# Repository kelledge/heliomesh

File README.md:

# Heliomesh

[Documentation](https://kelledge.github.io/heliomesh/)

Heliomesh is a growing collection of PCB designs that enable anyone to build robust solar-power
Meshtastic nodes.

As fun as it is to solder up a solution, these often end up being the weak point of any solution.
This project aims to provide fully integrated solutions that any one can order and pairs nicely
with the existing range of Meshtastic devices and enclosures.

## Contibuting
TODO

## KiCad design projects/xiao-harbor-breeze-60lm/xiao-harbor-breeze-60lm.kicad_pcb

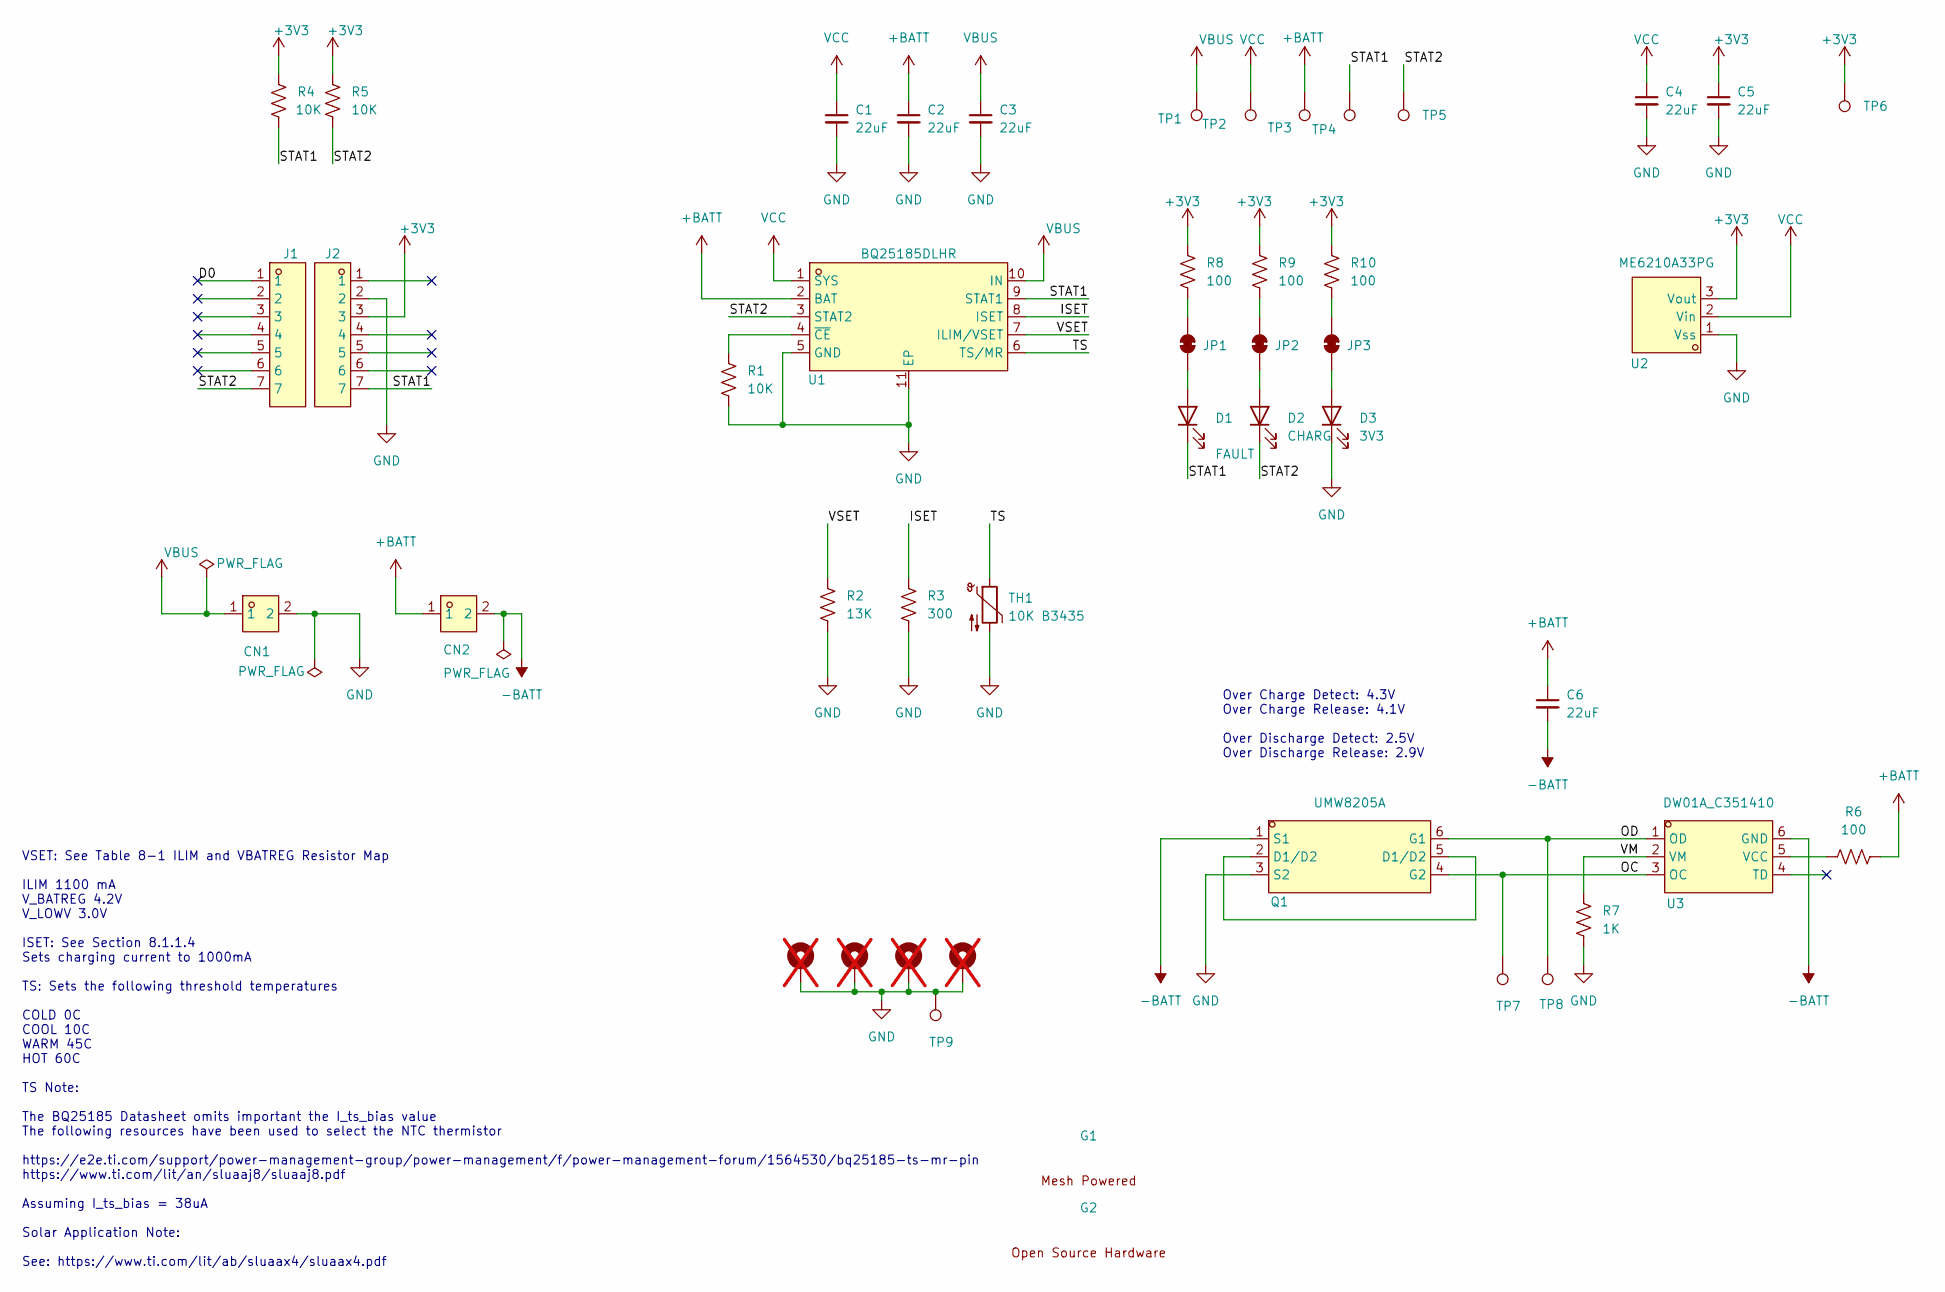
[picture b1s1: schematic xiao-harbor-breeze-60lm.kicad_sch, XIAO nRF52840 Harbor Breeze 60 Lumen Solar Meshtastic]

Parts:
C1, C2, C3, C4, C5, C6: 22uF; C_0805_2012Metric; JLCPCB PN C318688
CN1, CN2: XY122R-5.08-2P; CONN-TH_XY122R-5.08-2P; LCSC Part C784938
D1: FAULT; LED_0603_1608Metric; JLCPCB PN C965799
D2: CHARG; LED_0603_1608Metric; JLCPCB PN C965799
D3: 3V3; LED_0603_1608Metric; JLCPCB PN C965799
G1: mesh_pwrd_very_small
G2: oshw_very_small
H1, H2, H3, H4: MountingHole_Pad; MountingHole_3.2mm_M3_ISO7380_Pad; not fitted
J1, J2: 1165SDIG-07; HDR-TH_7P-P2.54-V-F; LCSC Part C2886701
JP1, JP2, JP3: SolderJumper_2_Bridged; SolderJumper-2_P1.3mm_Bridged_RoundedPad1.0x1.5mm
Q1: UMW8205A; SOT-23-6_L2.9-W1.6-P0.95-LS2.8-BL; LCSC Part C351449
R1, R4, R5: 10K; R_0603_1608Metric; JLCPCB PN C25804
R2: 13K; R_0603_1608Metric; JLCPCB PN C22797
R3: 300; R_0603_1608Metric; JLCPCB PN C23025
R6, R8, R9, R10: 100; R_0603_1608Metric; JLCPCB PN C22775
R7: 1K; R_0603_1608Metric; JLCPCB PN C21190
TH1: 10K B3435; R_0603_1608Metric; JLCPCB PN C153011
TP1, TP2, TP3, TP4, TP5, TP6, TP7, TP8, TP9: TestPoint; TestPoint_Pad_D1.5mm
U1: BQ25185DLHR; WSON-10_L2.2-W2.0-P0.40-BL-EP_TI_DLH0010A; LCSC Part C19725033
U2: ME6210A33PG; SOT-89_L4.5-W2.5-P1.50-LS4.2-BR; LCSC Part C85233
U3: DW01A_C351410; SOT-23-6_L2.9-W1.6-P0.95-LS2.8-BL; LCSC Part C351410

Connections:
+3V3: C5.1, J2.3, R4.1, R5.1, R8.1, R9.1, R10.1, TP6.1, U2.3 (Vout)
+BATT: C2.1, C6.1, CN2.1, R6.2, TP3.1, U1.2 (BAT)
-BATT: C6.2, CN2.2, Q1.1 (S1), U3.6 (GND)
/D0: J1.1
/ISET: R3.1, U1.8 (ISET)
/OC: Q1.4 (G2), TP7.1, U3.3 (OC)
/OD: Q1.6 (G1), TP8.1, U3.1 (OD)
/STAT1: D1.1 (K), J2.7, R4.2, TP4.1, U1.9 (STAT1)
/STAT2: D2.1 (K), J1.7, R5.2, TP5.1, U1.3 (STAT2)
/TS: TH1.1, U1.6 (TS/MR)
/VM: R7.1, U3.2 (VM)
/VSET: R2.1, U1.7 (ILIM/VSET)
GND: C1.2, C2.2, C3.2, C4.2, C5.2, CN1.2, D3.1 (K), H1.1, H2.1, H3.1, H4.1, J2.2, Q1.3 (S2), R1.2, R2.2, R3.2, R7.2, TH1.2, TP9.1, U1.5 (GND), U1.11 (EP), U2.1 (Vss)
unnamed: D1.2 (A), JP1.1 (A)
unnamed: D2.2 (A), JP2.1 (A)
unnamed: D3.2 (A), JP3.1 (A)
unnamed: JP1.2 (B), R8.2
unnamed: JP2.2 (B), R9.2
unnamed: JP3.2 (B), R10.2
unnamed: Q1.2 (D1/D2), Q1.5 (D1/D2)
unnamed: R1.1, U1.4 (~CE)
unnamed: R6.1, U3.5 (VCC)
VBUS: C3.1, CN1.1, TP1.1, U1.10 (IN)
VCC: C1.1, C4.1, TP2.1, U1.1 (SYS), U2.2 (Vin)

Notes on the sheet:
VSET: See Table 8-1 ILIM and VBATREG Resistor Map ILIM 1100 mA V_BATREG 4.2V V_LOWV 3.0V ISET: See Section 8.1.1.4 Sets charging current to 1000mA TS: Sets the following threshold temperatures COLD 0C COOL 10C WARM 45C HOT 60C TS Note: The BQ25185 Datasheet omits important the I_ts_bias value The f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
Over Charge Detect: 4.3V Over Charge Release: 4.1V Over Discharge Detect: 2.5V Over Discharge Release: 2.9V

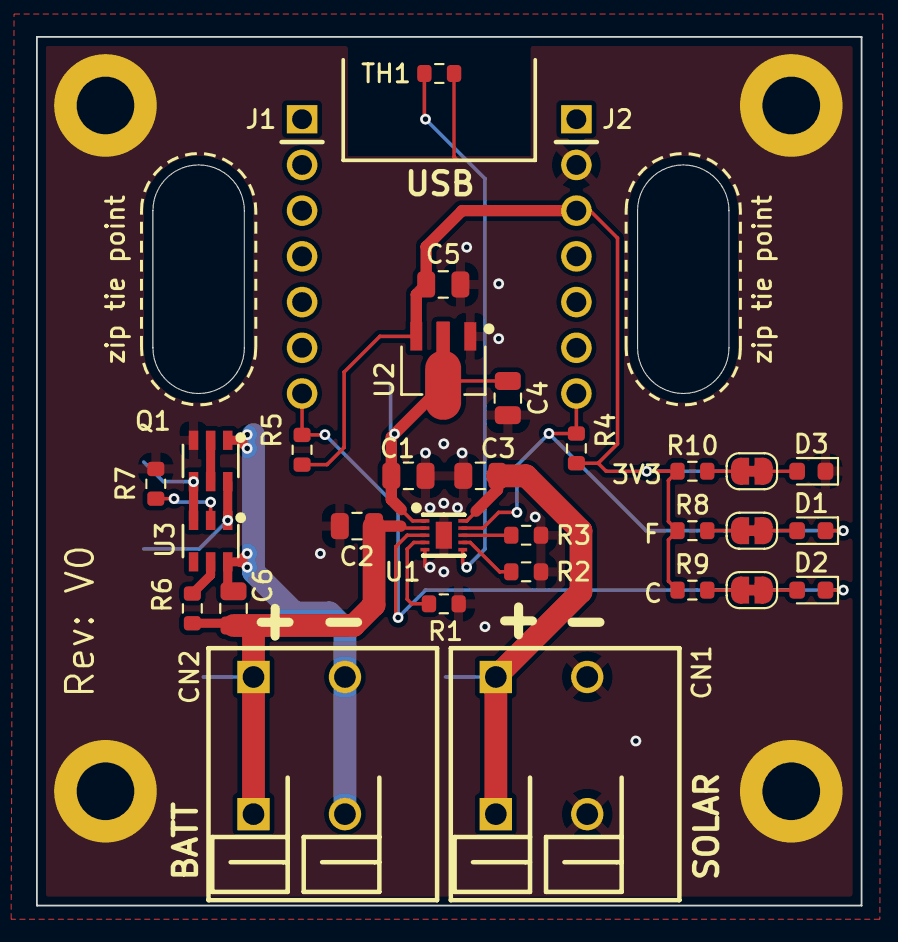
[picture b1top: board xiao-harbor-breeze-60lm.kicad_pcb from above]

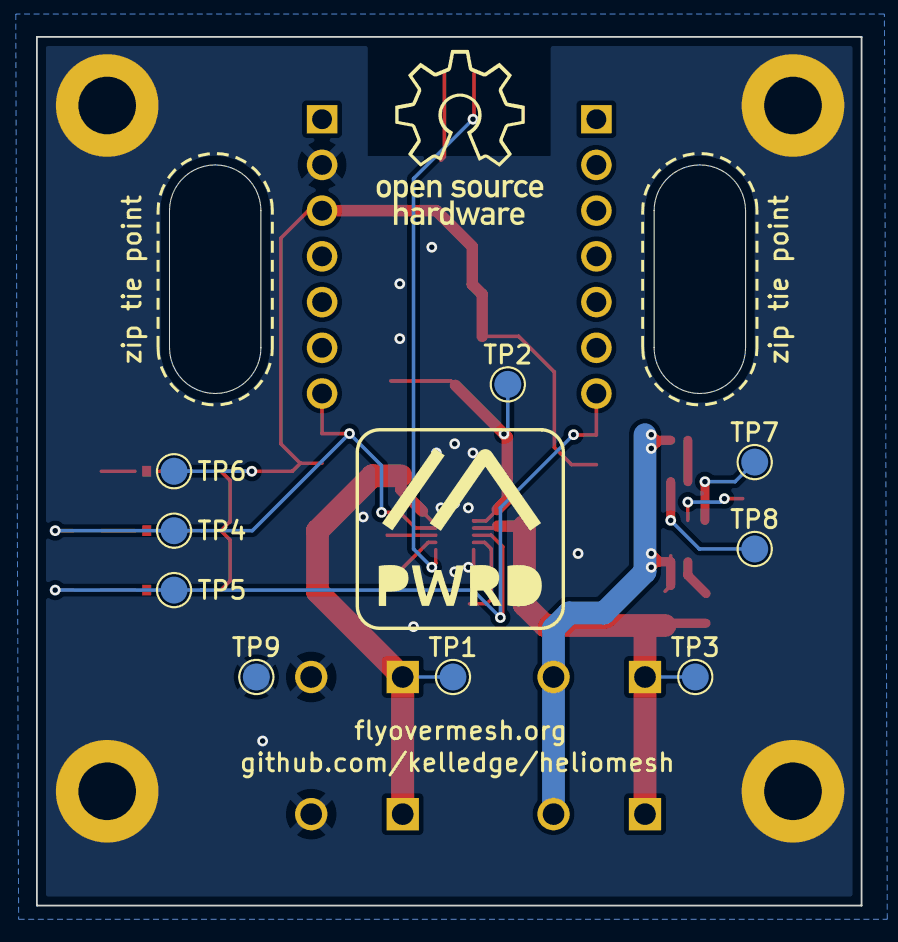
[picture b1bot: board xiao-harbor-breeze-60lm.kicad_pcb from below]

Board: 2 copper layers, 45.8 x 48.3 mm, 46 parts (11 on the bottom side), 23 nets.

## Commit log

2025-12-31 lib: Add DW01A and UMW8205A
    These two parts are the essential parts to the battery cell safety
    disconnect
2025-12-31 Add low voltage and over voltage protection
    This part is a final safety net for battery charage management.
    It is configured to have a low voltage cutoff of 2.5V and an over
    voltage cutoff of 4.3V.
    These values are comfortably outside the range of the change controller
    thresholds, but still within the ranges generally accepted to avoid
    permanent cell damage.
2025-12-31 Add ziptie mounting slots
2025-12-31 Use horizontally oriented spring terminals
2025-12-31 Address build warning: Missing `Mechanical` library
2025-12-31 Organize project symbol and footprints
2025-12-31 Add test points and status LEDs
    LEDs allow simple confirmation of the board state. Cut their traces
    after testing to save around 20mW of power draw.
    Added test points to important signals to speed up diagnosing any issues
    with the initial design.
    Minor update to README.md
2025-12-31 Add user documented LED jumpers
    Indicates to users that the LEDs are optional and documents how and
    where to cut to conserve power.
2025-12-31 Add release job
2025-12-31 Drop graphics from BOM
2026-01-02 Add additional documentation artifacts
    * Exports glb 3D model: This is a format suitable for use with
    https://github.com/google/model-viewer
    * Exports kicanvas for interactive web view of schematic and pcb
    * Initialize MkDocs for static documentation site generator
    * Add custom `on_files` hook to move kibot assets to generated site
    * Extend workflow to publish pages
2026-01-02 Fix GLB output; Vendor all libraries
    The kicad binaries for Ubuntu 24.04 are linked against a buggy version
    of OCCT. The most direct solution here was simply to upgrade to Ubuntu 25.04.
    Additionally all referenced libraries are now vendored under lib/. This
    ensures that there are no conflicts between the container definition and
    the host.
    Due to this, the entire lib/ directory is now tracked in git lfs.
2026-01-02 Drop workflow path predicate; Attempt to solve documentation link
    Dropping the workflow path predicate for the moment. It has no use
    currently while only a single project is hosted.
2026-01-02 Add zip-tie PCB documentation
    Documents the purpose of the PCB cutout regions. Intended for users to
    pass a zip-tie through and around to secure the XIAO development kit.
